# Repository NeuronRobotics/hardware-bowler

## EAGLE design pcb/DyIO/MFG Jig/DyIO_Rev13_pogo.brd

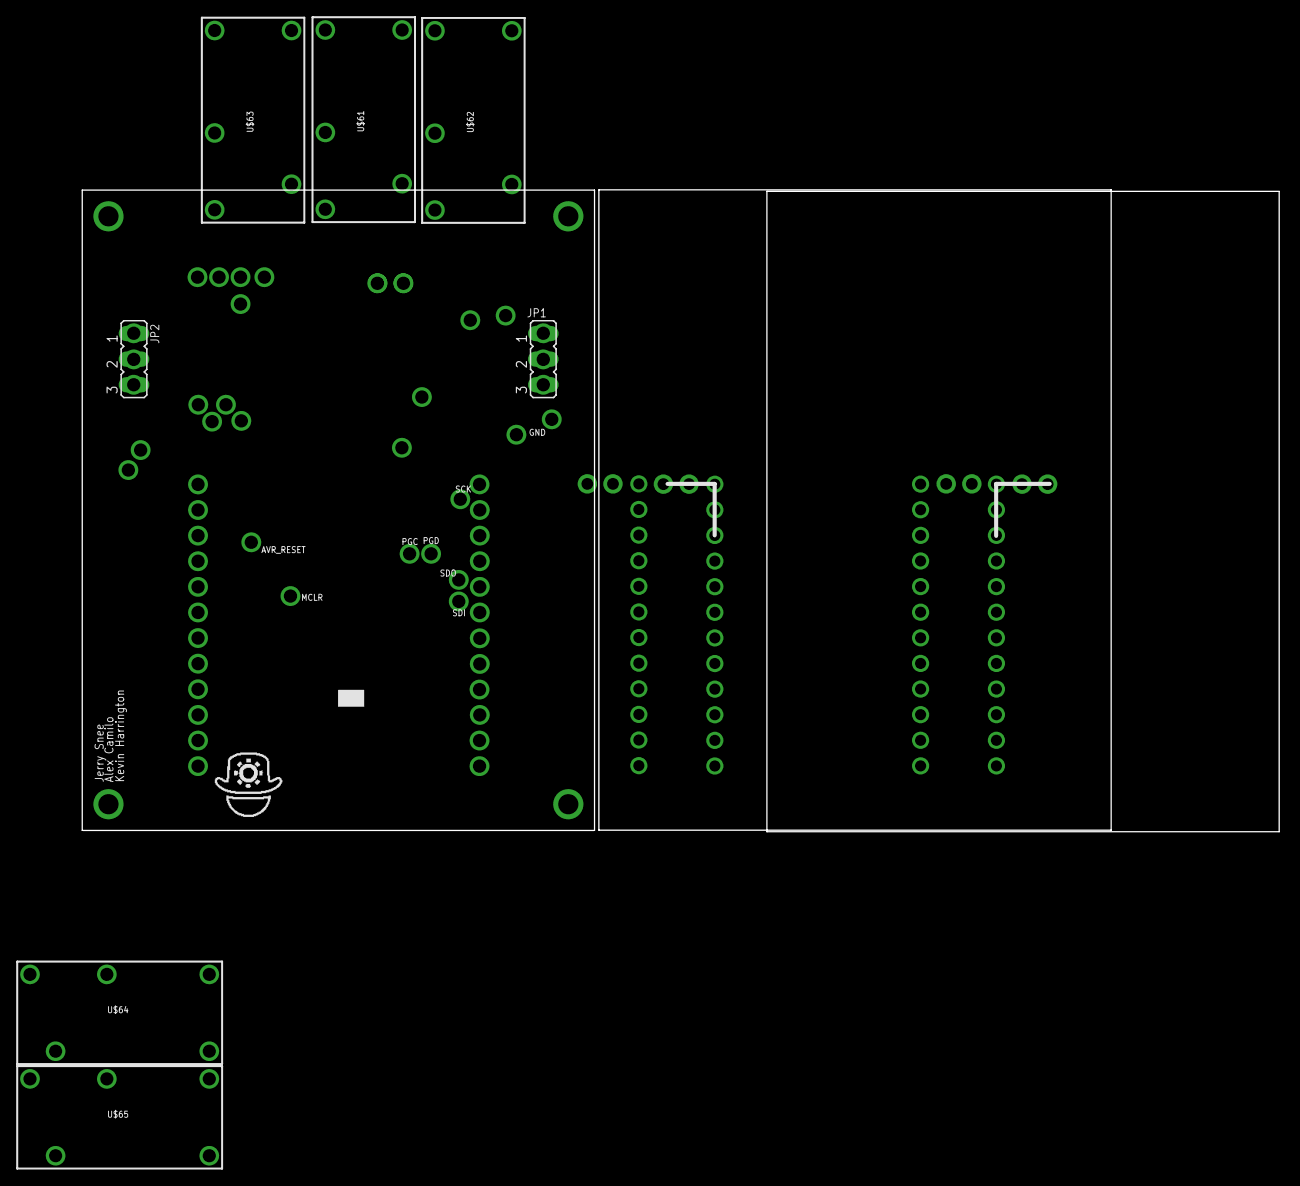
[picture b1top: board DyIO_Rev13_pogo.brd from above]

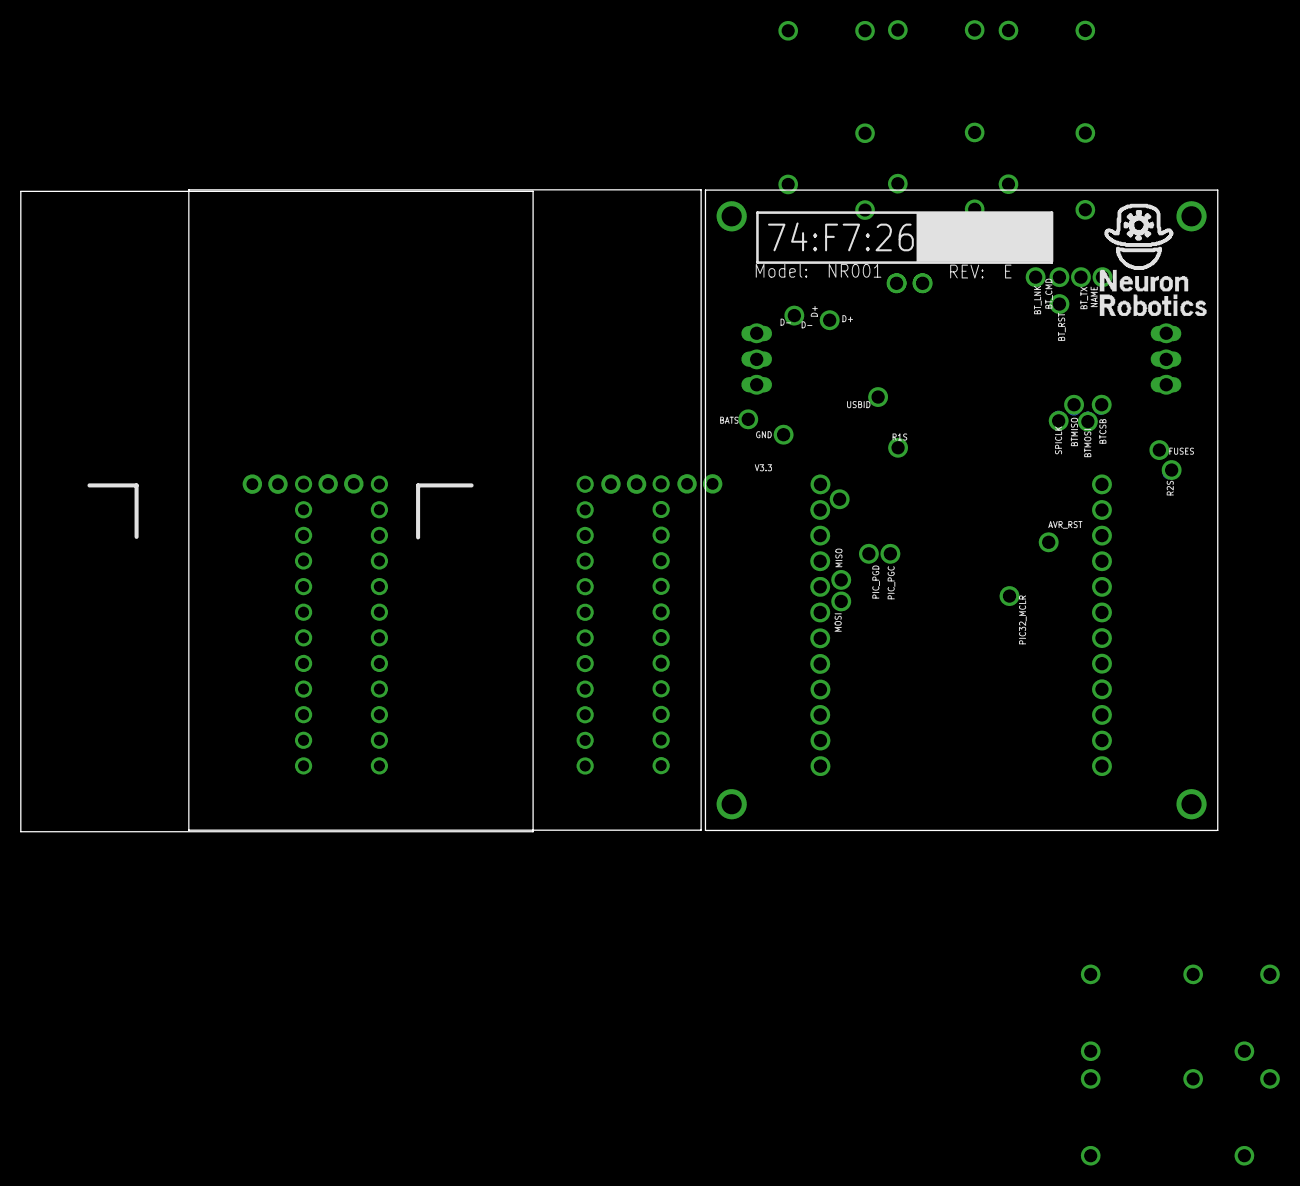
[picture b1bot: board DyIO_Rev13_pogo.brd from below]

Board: 4 copper layers, 118.7 x 63.7 mm, 99 parts (18 on the bottom side), 34 nets, no tracks yet.

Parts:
AVR_RESET: PTR1TP14R; TP14R
BATS: PTR1TP14R; TP14R
BTCSB: PTR1TP14R; TP14R
BTMISO: PTR1TP14R; TP14R
BTMOSI: PTR1TP14R; TP14R
BT_CMD: PTR1TP14R; TP14R
BT_LNK: PTR1TP14R; TP14R
BT_RST: PTR1TP14R; TP14R
BT_TX: PTR1TP14R; TP14R
D+: PTR1TP14R; TP14R
D-: PTR1TP14R; TP14R
FUSES: PTR1TP14R; TP14R
GND: PTR1B1,27; B1,27
JP1, JP2: JP2
MCLR: PTR1TP14R; TP14R
NAME: PTR1TP14R; TP14R
PGC: PTR1TP14R; TP14R
PGD: PTR1TP14R; TP14R
R1S, R2S: PTR1TP14R; TP14R
SCK: PTR1TP14R; TP14R
SDI: PTR1TP14R; TP14R
SDO: PTR1TP14R; TP14R
SPICLK: PTR1TP14R; TP14R
U4, U5, U15, U16: 1X12
U$1, U$2, U$6, U$7, U$8, U$9, U$10, U$11, U$12, U$13, U$14, U$15, U$16, U$17, U$18, U$20, U$21, U$22, U$23, U$24, U$25, U$26, U$27, U$28: POGO-TIP; POGO
U$5, U$66, U$67: OUTLINE
U$19, U$68, U$69, U$70, U$71: 2P; 2PTH
U$29, U$30, U$31, U$32, U$33, U$34, U$35, U$36, U$37, U$38, U$39, U$40, U$41, U$42, U$43, U$44, U$45, U$46, U$47, U$48, U$49, U$50, U$51, U$52, U$53, U$54, U$55, U$56, U$57, U$58, U$59, U$60: POGO-CUP; POGO
U$61, U$62, U$63, U$64, U$65: RELAYPTH; RELAY-G5Q
USBID: PTR1TP14R; TP14R

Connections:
5V: JP1.1, JP2.1
AVR_RESET: AVR_RESET.TP, U$2.P$1
BTCSB: BTCSB.TP, U$25.P$1
BTMISO: BTMISO.TP, U$23.P$1
BTMOSI: BTMOSI.TP, U$24.P$1
CON_ADC0: U4.P9, U15.P9
CON_ADC1: U4.P10, U15.P10
CON_ADC2: U4.P11, U15.P11
CON_ADC3: U4.P12, U15.P12
CON_ADC4: U5.P1, U16.P1
CON_ADC5: U5.P2, U16.P2
CON_ADC6: U5.P3, U16.P3
CON_ADC7: U5.P4, U16.P4
CON_INT0: U5.P6, U16.P6
CON_INT1: U5.P8, U16.P8
CON_INT2: U5.P10, U16.P10
CON_INT3: U5.P12, U16.P12
CON_IO0: U5.P5, U16.P5
CON_IO1: U5.P7, U16.P7
CON_IO2: U5.P9, U16.P9
CON_IO3: U5.P11, U16.P11
CON_PWM0: U4.P7, U15.P7
CON_PWM1: U4.P8, U15.P8
CON_PWM2: U4.P6, U15.P6
CON_PWM3: U4.P5, U15.P5
CON_SCK: U4.P1, U15.P1
CON_SPI_CS: U4.P4, U15.P4
FUSED_VDD: JP1.3, JP2.3
GND: GND.PP, U$11.P$1, U$19.P$2
MISO: U4.P2, U15.P2
MOSI: U4.P3, U15.P3
unnamed: U$61.2, U$62.2
unnamed: U$64.2, U$65.2
SPICLK: SPICLK.TP, U$22.P$1

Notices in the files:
parts and their libraries:
SparkFun-Electromechanical: Licensing: Creative Commons ShareAlike 4.0 International - https://creativecommons.org/licenses/by-sa/4.0
